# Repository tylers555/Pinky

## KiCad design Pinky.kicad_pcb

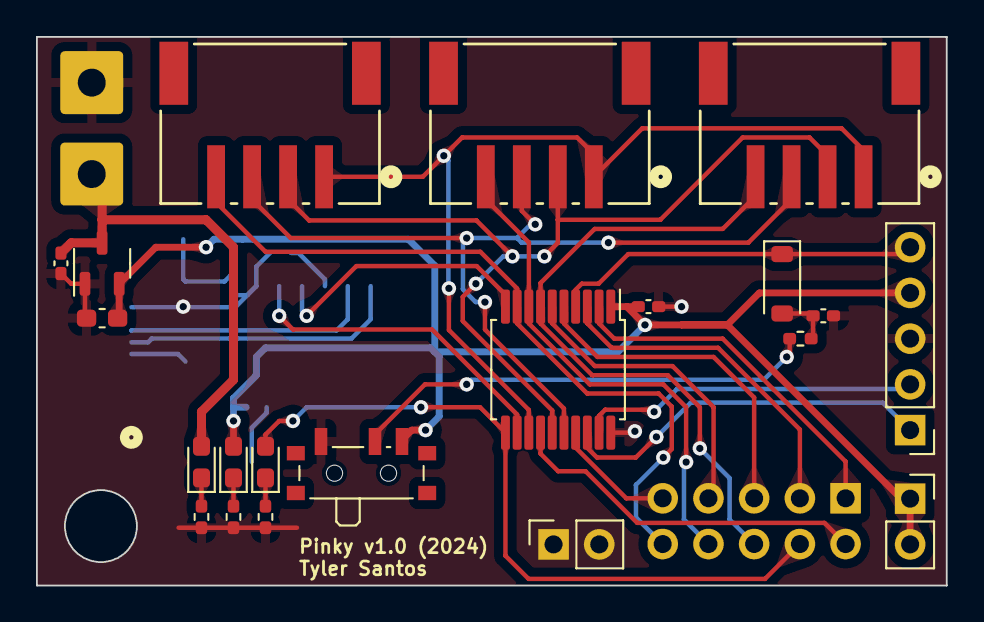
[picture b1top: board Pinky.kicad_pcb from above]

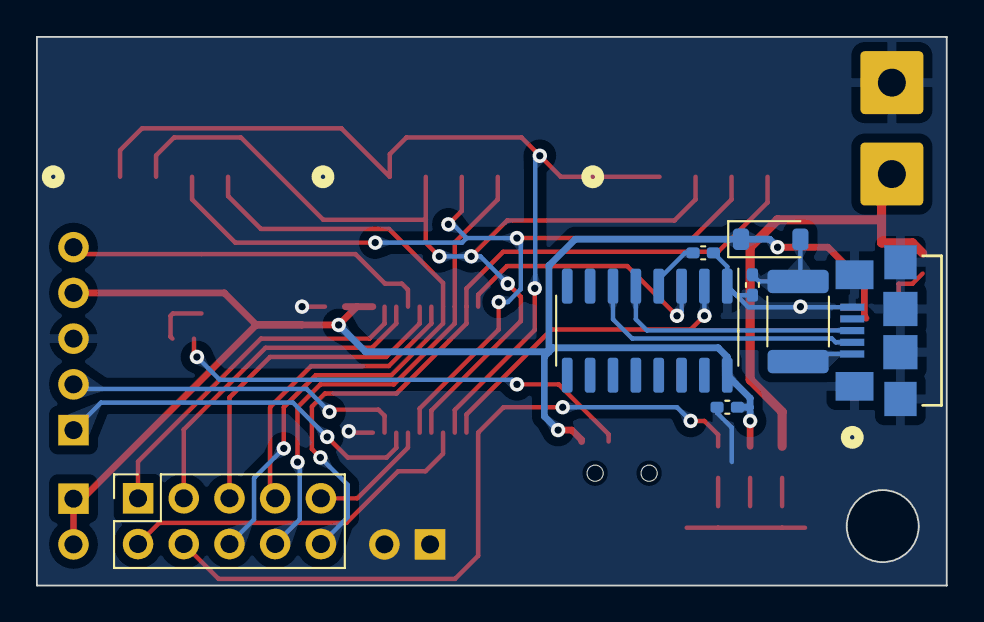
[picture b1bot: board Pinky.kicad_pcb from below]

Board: 2 copper layers, 50.5 x 30.5 mm, 31 parts (8 on the bottom side), 31 nets.

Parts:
C1, C3, C5: 0.1u; C_0402_1005Metric_Pad0.74x0.62mm_HandSolder
C2: 10n; C_0402_1005Metric_Pad0.74x0.62mm_HandSolder
C4: 150n; C_0402_1005Metric_Pad0.74x0.62mm_HandSolder
C_in1: 1u; C_0402_1005Metric_Pad0.74x0.62mm_HandSolder
C_out2: 10u; C_0603_1608Metric_Pad1.08x0.95mm_HandSolder
D1, D5: D_Schottky; D_SOD-123
D2: Gstat; LED_0603_1608Metric_Pad1.05x0.95mm_HandSolder
D3: PWR stat; LED_0603_1608Metric_Pad1.05x0.95mm_HandSolder
D4: 5Vstat; LED_0603_1608Metric_Pad1.05x0.95mm_HandSolder
F1: Polyfuse; Fuse_1812_4532Metric_Pad1.30x3.40mm_HandSolder
IC1: PIC16F15243-I_SS; SSOP-20_5.3x7.2mm_P0.65mm
IC2: ZXTR2105FQ-7; SOT-23-3
J1: +Batt; SolderWire-0.75sqmm_1x01_D1.25mm_OD3.5mm
J2: -Batt; SolderWire-0.75sqmm_1x01_D1.25mm_OD3.5mm
J3: ICSP; PinHeader_1x05_P2.54mm_Vertical
J4, J5, J6: Conn_01x04_Socket; CONN_S4B-PH-SM4-TBLFSN_JST
J7: GPIO; PinSocket_2x05_P2.54mm_Vertical
J8: USB_B_Micro; CONN_10118192-0002LF_AMP
J10: 5V; PinSocket_1x02_P2.54mm_Vertical
J11: GND; PinSocket_1x02_P2.54mm_Vertical
R1: 10k; R_0402_1005Metric_Pad0.72x0.64mm_HandSolder
R2, R7: 220; R_0402_1005Metric_Pad0.72x0.64mm_HandSolder
R6: 2.2k; R_0402_1005Metric_Pad0.72x0.64mm_HandSolder
SW1: SW_SPDT; SW_SPDT_PCM12
U1: CH340C; SOIC-16_3.9x9.9mm_P1.27mm

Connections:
5V: C1.1, C5.1, C_out2.1, D4.2 (A), D5.1 (K), IC1.1 (VDD), IC2.2 (VOUT), J3.4, J10.1, J10.2, SW1.3 (C), U1.16 (VCC)
GND: C1.2, C2.2, C3.1, C4.2, C5.2, C_in1.2, C_out2.2, IC1.20 (VSS), IC2.1 (GND), J2.1, J3.3, J8.5 (GND), J8.6 (Shield), J8.7, J8.9, J8.11, J11.1, J11.2, R2.1, R6.1, R7.1, SW1.1 (A), U1.1 (GND)
GPIO_0: IC1.2 (RA5), J7.1
GPIO_1: IC1.3 (RA4), J7.3
GPIO_2: IC1.5 (RC5), J7.5
GPIO_3: IC1.6 (RC4), J7.7
GPIO_4: IC1.17 (RA2), J7.9
GPIO_5: IC1.14 (RC2), J7.2
GPIO_6: D2.2 (A), IC1.11 (RB6), J7.4
unnamed: C2.1, D1.2 (A), R1.2
unnamed: D1.1 (K), IC1.4 (~MCLR/VPP/RA3), J3.5
unnamed: D2.1 (K), R2.2
unnamed: D3.1 (K), R6.2
unnamed: D4.1 (K), R7.2
unnamed: C4.1, D5.2 (A), F1.1
unnamed: IC1.19 (RA0/ICSPDAT), J3.2
unnamed: IC1.18 (RA1/ICSPCLK), J3.1
unnamed: J8.3 (D+), U1.5 (UD+)
unnamed: J8.2 (D-), U1.6 (UD-)
unnamed: R1.1, SW1.2 (B)
unnamed: C3.2, U1.4 (V3)
PWR: C_in1.1, D3.2 (A), IC2.3 (VIN), J1.1
RX: IC1.12 (RB5), U1.2 (TXD)
SCK: IC1.13 (RB4), J4.1, J5.1, J6.1
SDI: IC1.16 (RC0), J4.3, J5.3, J6.3
SDO: IC1.15 (RC1), J4.2, J5.2, J6.2
SPI_0: IC1.7 (RC3), J4.4, J7.6
SPI_1: IC1.8 (RC6), J5.4, J7.8
SPI_2: IC1.9 (RC7), J6.4, J7.10
TX: IC1.10 (RB7), U1.3 (RXD)
VBUS: F1.2, J8.1 (VBUS)

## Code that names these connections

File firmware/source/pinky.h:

#ifndef PINKY_H
#define PINKY_H

#include <xc.h>

#define _XTAL_FREQ 32000000

#define ISR_ADDRESS     1024
#define STARTUP_ADDRESS  512
#define LOOP_ADDRESS     640

#define GPIO_0 PORTAbits.RA5
#define GPIO_1 PORTAbits.RA4
#define GPIO_2 PORTCbits.RC5
#define GPIO_3 PORTCbits.RC4
#define GPIO_4 PORTAbits.RA2
#define GPIO_5 PORTCbits.RC2
#define GPIO_6 PORTBbits.RB6
#define GPIO_7 PORTCbits.RC3
#define GPIO_8 PORTCbits.RC6
#define GPIO_9 PORTCbits.RC7

#define SPI_0 GPIO_7
#define SPI_1 GPIO_8
#define SPI_2 GPIO_9

#define STAT_LED GPIO_6

typedef __bit b1;

typedef uint8_t u8;
typedef uint16_t u16;
typedef uint32_t u32;

typedef int8_t  s8;
typedef int16_t s16;
typedef int32_t s32;

void stat_blink(int times, int delay);

#endif //PINKY_H
